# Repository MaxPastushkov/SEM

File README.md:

### Repo for all things related to the garage SEM (ISI DS-130C) ###

All documentation for this SEM and many, many others can be found [here](https://drive.google.com/drive/folders/1kHMsw_-iYlvwElDAo1szjx7huENmmcO2?usp=sharing)

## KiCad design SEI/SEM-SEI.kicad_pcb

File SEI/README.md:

Secondary Electron Imaging preamp (reverse-engineered)

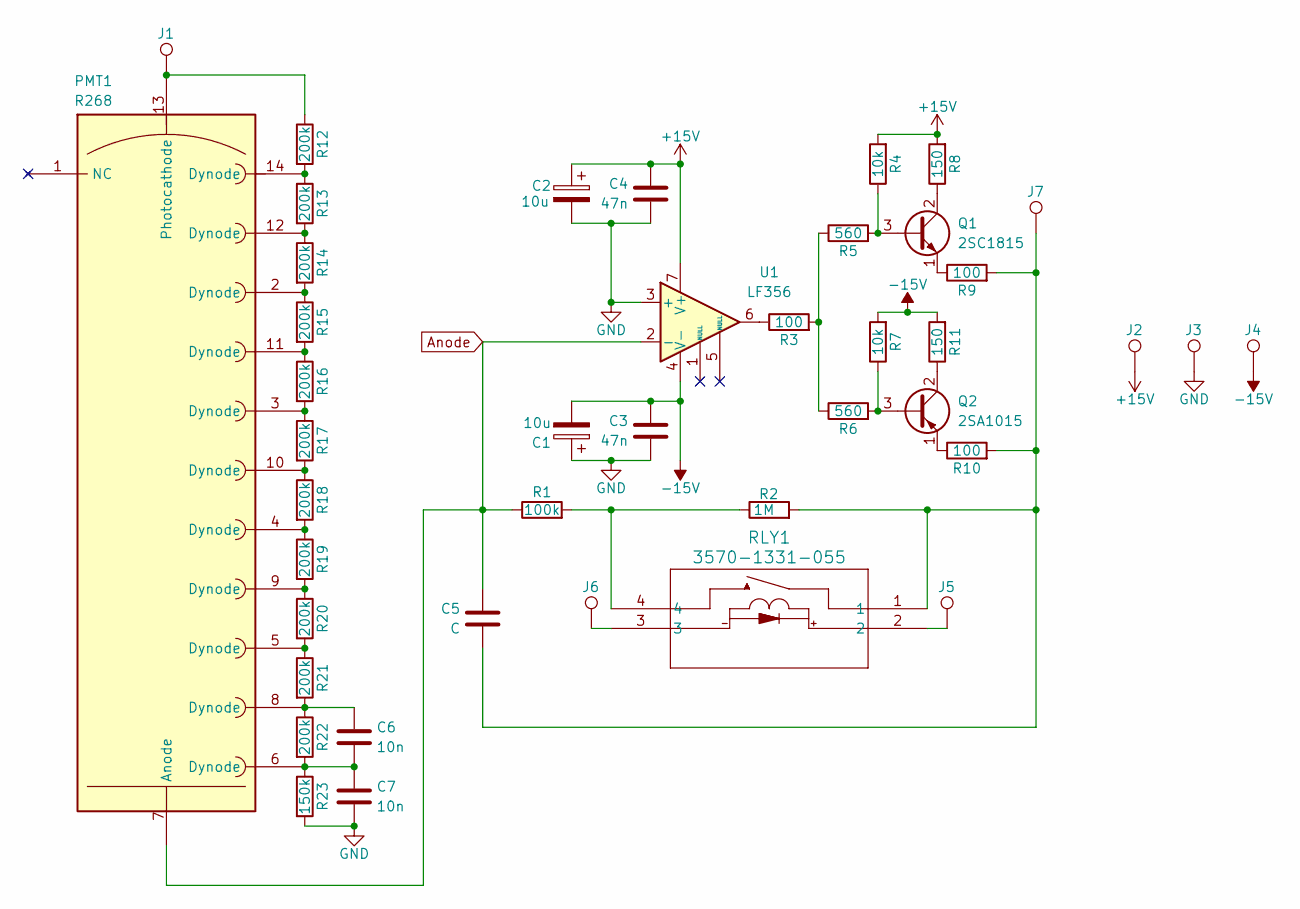
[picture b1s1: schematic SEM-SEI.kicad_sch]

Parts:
C1, C2: 10u; C_1206_3216Metric
C3, C4: 47n; C_1206_3216Metric
C5: C; C_1206_3216Metric
C6, C7: 10n; C_1808_4520Metric
J1, J2, J3, J4, J5, J6, J7: Pin_D1.0mm_L10.0mm
PMT1: R268; B14B
Q1: 2SC1815; SOT-23-3
Q2: 2SA1015; SOT-23-3
R1: 100k; R_1206_3216Metric
R2: 1M; R_1206_3216Metric
R3, R9, R10: 100; R_1206_3216Metric
R4, R7: 10k; R_1206_3216Metric
R5, R6: 560; R_1206_3216Metric
R8, R11: 150; R_1206_3216Metric
R12, R13, R14, R15, R16, R17, R18, R19, R20, R21, R22: 200k; R_2010_5025Metric
R23: 150k; R_2010_5025Metric
RLY1: 3570-1331-055; SIP_3570-1331_COM
U1: LF356; SOIC-8_3.9x4.9mm_P1.27mm

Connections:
+15V: C2.1, C4.1, J2.1, R4.2, R8.2, U1.7 (V+)
-15V: C1.2, C3.1, J4.1, R7.2, R11.2, U1.4 (V-)
Anode: C5.1, PMT1.7 (Anode), R1.1, U1.2 (-)
GND: C1.1, C2.2, C3.2, C4.2, C7.2, J3.1, R23.2, U1.3 (+)
unnamed: C5.2, J7.1, R2.2, R9.2, R10.2, RLY1.1
unnamed: C6.1, PMT1.8 (Dynode), R21.2, R22.1
unnamed: C6.2, C7.1, PMT1.6 (Dynode), R22.2, R23.1
unnamed: J5.1, RLY1.2
unnamed: J6.1, RLY1.3
unnamed: PMT1.2 (Dynode), R14.2, R15.1
unnamed: PMT1.3 (Dynode), R16.2, R17.1
unnamed: PMT1.4 (Dynode), R18.2, R19.1
unnamed: PMT1.5 (Dynode), R20.2, R21.1
unnamed: PMT1.9 (Dynode), R19.2, R20.1
unnamed: PMT1.10 (Dynode), R17.2, R18.1
unnamed: PMT1.11 (Dynode), R15.2, R16.1
unnamed: PMT1.12 (Dynode), R13.2, R14.1
unnamed: PMT1.14 (Dynode), R12.2, R13.1
unnamed: J1.1, PMT1.13 (Photocathode), R12.1
unnamed: Q1.3 (B), R4.1, R5.2
unnamed: Q1.2 (C), R8.1
unnamed: Q1.1 (E), R9.1
unnamed: Q2.3 (B), R6.2, R7.1
unnamed: Q2.2 (C), R11.1
unnamed: Q2.1 (E), R10.1
unnamed: R1.2, R2.1, RLY1.4
unnamed: R3.1, U1.6
unnamed: R3.2, R5.1, R6.1

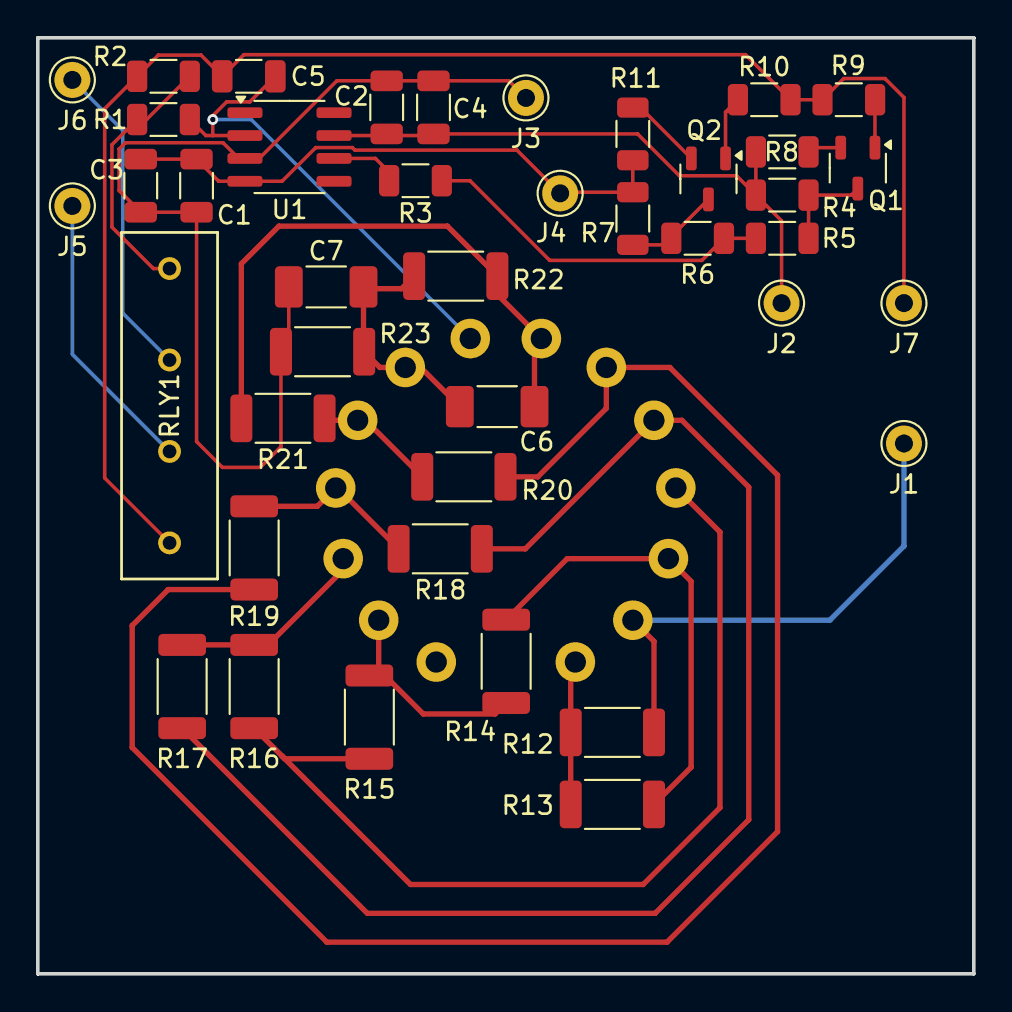
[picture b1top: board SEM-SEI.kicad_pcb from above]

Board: 2 copper layers, 52.0 x 52.0 mm, 42 parts (1 on the bottom side), 28 nets.

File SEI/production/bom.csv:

Designator,Footprint,Quantity,Value,LCSC Part #
"C1, C2",1206,2,10u,
"C3, C4",1206,2,47n,
C5,1206,1,C,
"C6, C7",1808,2,10n,
"J1, J2, J3, J4, J5, J6, J7",Pin_D1.0mm_L10.0mm,7,~,
PMT1,B14B,1,R268,
Q1,SOT-23-3,1,2SC1815,
Q2,SOT-23-3,1,2SA1015,
R1,1206,1,100k,
"R10, R3, R9",1206,3,100,
"R11, R8",1206,2,150,
"R12, R13, R14, R15, R16, R17, R18, R19, R20, R21, R22",2010,11,200k,
R2,1206,1,1M,
R23,2010,1,150k,
"R4, R7",1206,2,10k,
"R5, R6",1206,2,560,
RLY1,SIP_3570-1331_COM,1,3570-1331-055,
U1,SOIC-8_3.9x4.9mm_P1.27mm,1,LF356,

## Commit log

2026-04-03 Add stuff
2026-04-03 Add image
2026-04-03 Add schematics
2026-04-03 Move image
2026-04-03 Add diffusion pump catalog
